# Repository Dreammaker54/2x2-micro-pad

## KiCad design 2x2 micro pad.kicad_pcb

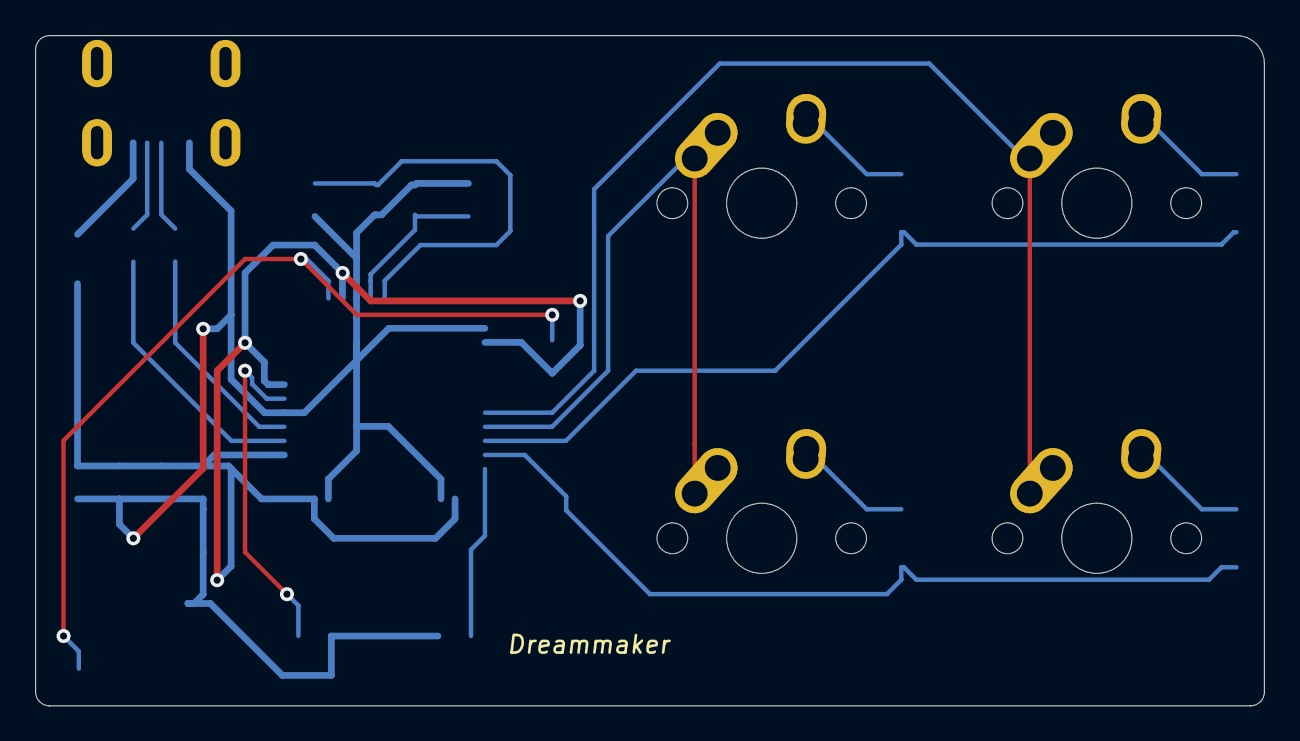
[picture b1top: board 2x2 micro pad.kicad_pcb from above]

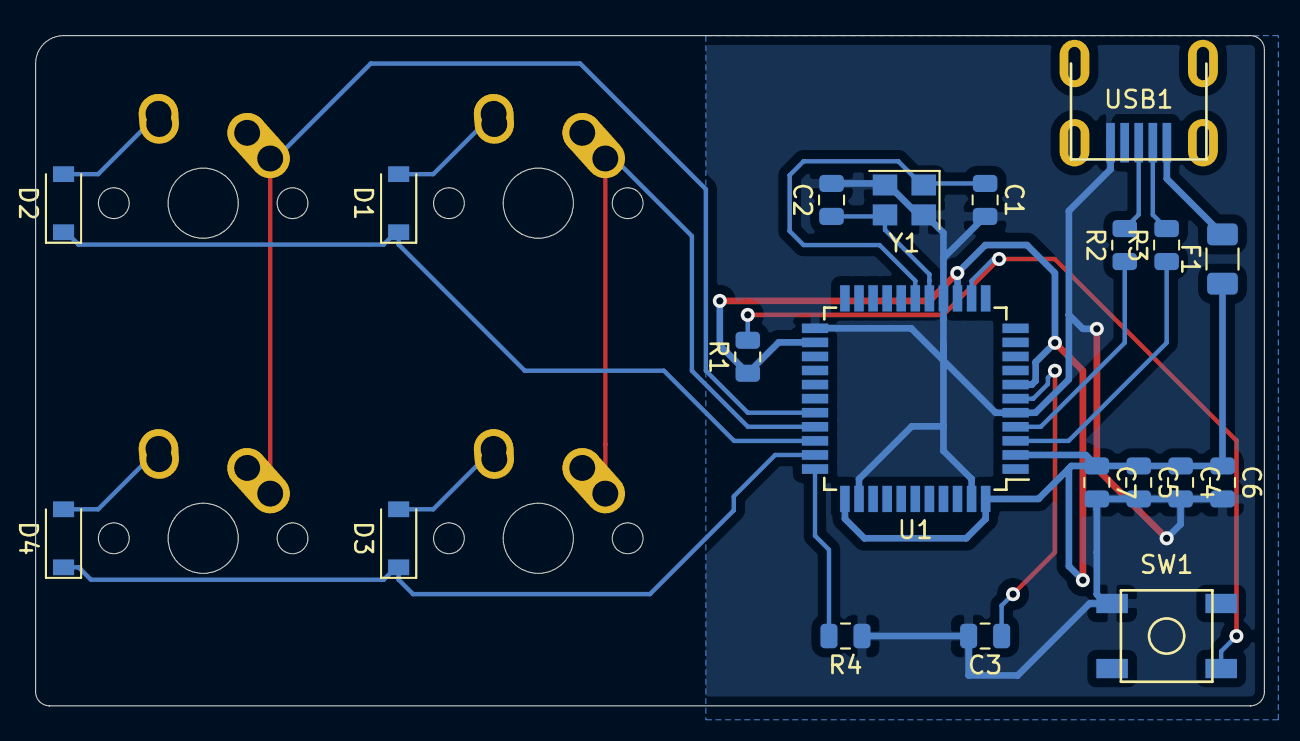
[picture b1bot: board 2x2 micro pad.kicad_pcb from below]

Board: 2 copper layers, 69.8 x 38.1 mm, 24 parts (20 on the bottom side), 20 nets.

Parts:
C1, C2: 22pF; C_0805_2012Metric
C3: 1uF; C_0805_2012Metric
C4, C5, C6: 0.1uF; C_0805_2012Metric
C7: 10uF; C_0805_2012Metric
D1, D2, D3, D4: D_Small; D_SOD-123
F1: 500mA; Fuse_1206_3216Metric
MX1, MX2, MX3, MX4: MX-NoLED; MX-1U-NoLED
R1, R4: 10k; R_0805_2012Metric
R2, R3: 22; R_0805_2012Metric
SW1: SW_Push; SKQG-1155865
U1: ATmega32U4-AU; TQFP-44_10x10mm_P0.8mm
USB1: Molex-0548190589
Y1: 16MHz; Crystal_SMD_3225-4Pin_3.2x2.5mm

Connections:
+5V: C4.1, C5.1, C6.1, C7.1, F1.1, R1.1, U1.2, U1.7, U1.14, U1.24, U1.34, U1.44
COL0: MX1.1, MX3.1, U1.30
COL1: MX2.1, MX4.1, U1.29
D+: R2.2, USB1.3
D-: R3.2, USB1.4
GND: C1.2, C2.2, C3.2, C4.2, C5.2, C6.2, C7.2, R4.1, SW1.1, U1.5, U1.15, U1.23, U1.35, U1.43, USB1.1, Y1.2, Y1.4
unnamed: C1.1, U1.17, Y1.1
unnamed: C2.1, U1.16, Y1.3
unnamed: C3.1, U1.6
unnamed: D1.2, MX1.2
unnamed: D2.2, MX2.2
unnamed: D3.2, MX3.2
unnamed: D4.2, MX4.2
unnamed: R1.2, SW1.2, U1.13
unnamed: R2.1, U1.4
unnamed: R3.1, U1.3
unnamed: R4.2, U1.33
ROW0: D1.1, D2.1, U1.31
ROW1: D3.1, D4.1, U1.32
VCC: F1.2, USB1.5

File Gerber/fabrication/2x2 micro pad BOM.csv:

"Id";"Designator";"Package";"Quantity";"Designation";"Supplier and ref";
1;"G***";"juhua1";1;"LOGO";;;
2;"MX4,MX3,MX2,MX1";"MX-1U-NoLED";4;"MX-NoLED";;;
3;"Y1";"Crystal_SMD_3225-4Pin_3.2x2.5mm";1;"16MHz";;;
4;"USB1";"Molex-0548190589";1;"Molex-0548190589";;;
5;"U1";"TQFP-44_10x10mm_P0.8mm";1;"ATmega32U4-AU";;;
6;"SW1";"SKQG-1155865";1;"SW_Push";;;
7;"R4,R1";"R_0805_2012Metric";2;"10k";;;
8;"R3,R2";"R_0805_2012Metric";2;"22";;;
9;"F1";"Fuse_1206_3216Metric";1;"500mA";;;
10;"D4,D3,D2,D1";"D_SOD-123";4;"D_Small";;;
11;"C7";"C_0805_2012Metric";1;"10uF";;;
12;"C6,C5,C4";"C_0805_2012Metric";3;"0.1uF";;;
13;"C3";"C_0805_2012Metric";1;"1uF";;;
14;"C2,C1";"C_0805_2012Metric";2;"22pF";;;

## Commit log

2020-09-25 Initialize project
2020-09-25 use local lib
2020-09-25 sch done
2020-09-25 pcb 2
2020-09-25 pcb routing
2020-09-25 pcb update
2020-09-25 gerber
